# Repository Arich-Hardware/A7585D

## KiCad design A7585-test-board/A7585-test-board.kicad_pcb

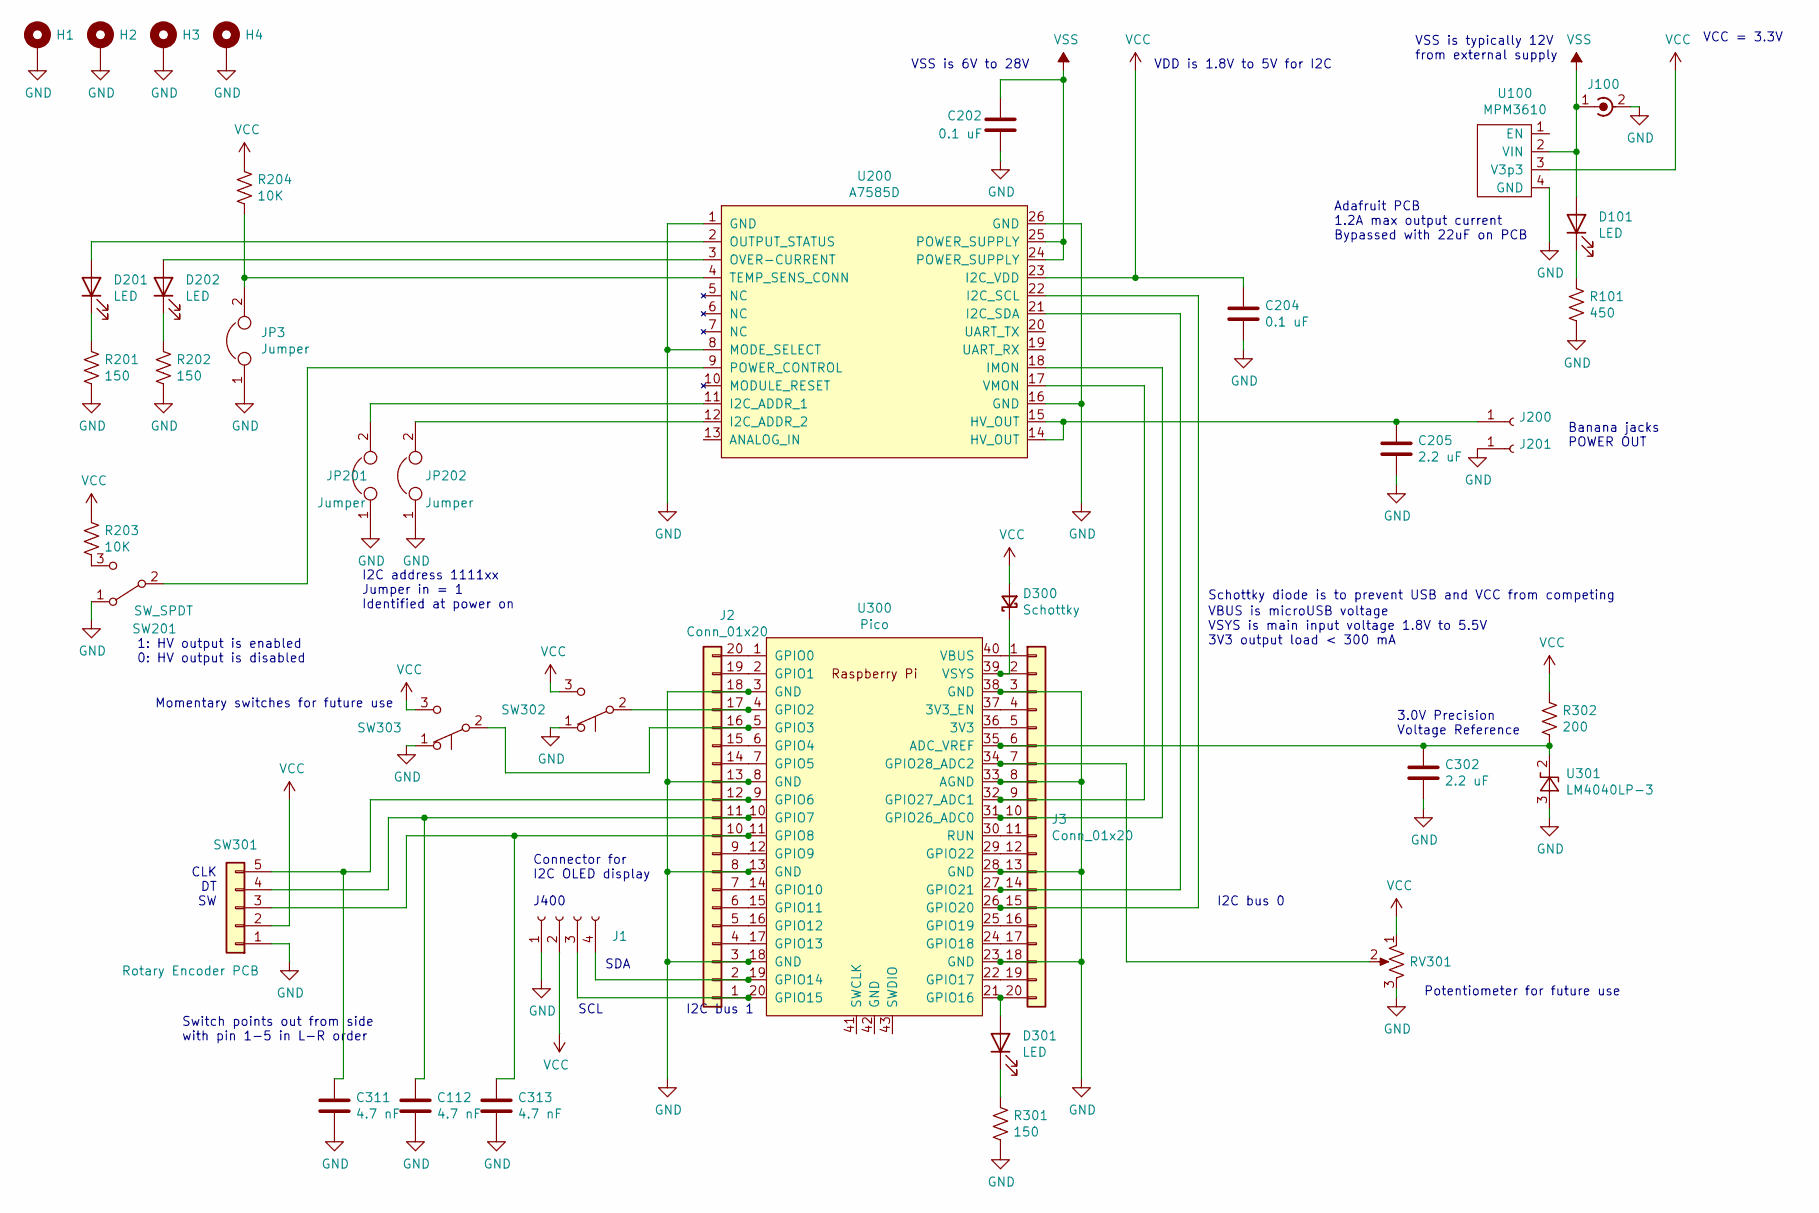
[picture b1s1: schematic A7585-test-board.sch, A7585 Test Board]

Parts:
C112, C311, C313: 4.7 nF; C_1206_3216Metric
C202, C204: 0.1 uF; C_1206_3216Metric
C205, C302: 2.2 uF; C_1206_3216Metric
D101, D201, D202, D301: LED; LED_D4.0mm
D300: Schottky; LED_D4.0mm
H1, H2, H3, H4: MountingHole_Pad; MountingHole_3.2mm_M3_Pad
J1: Conn_01x04_Female; Connector_Strip
J2, J3: Conn_01x20; PinHeader_1x20_P2.54mm_Vertical
J100: Conn_Coaxial_Power; BarrelJack_Horizontal
J200, J201: Conn_01x01_Female; Bannana_Jack_2pin
JP3, JP201, JP202: Jumper; PinHeader_1x02_P2.54mm_Vertical
R101: 450; R_1206_3216Metric
R201, R202, R301: 150; R_1206_3216Metric
R203, R204: 10K; R_1206_3216Metric
R302: 200; R_1206_3216Metric
RV301: R_POT_US; Potentiometer_Piher_T-16H_Single_Horizontal
SW201: SW_SPDT; SW_DIP_SPSTx01_Slide_9.78x4.72mm_W7.62mm_P2.54mm
SW301: Rotary Encoder PCB; PinHeader_1x05_P2.54mm_Vertical
SW302, SW303: SW_Push_SPDT; Push_Button
U100: MPM3610
U200: A7585D; A7585D_Board
U300: Pico; RPi_Pico_SMD_TH
U301: LM4040LP-3; TO-92_Inline

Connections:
GND: C112.2, C202.2, C204.2, C205.2, C302.2, C311.2, C313.2, H1.1, H2.1, H3.1, H4.1, J1.1, J2.3, J2.8, J2.13, J2.18, J3.3, J3.8, J3.13, J3.18, J100.2 (Ext), J201.1, JP3.1, JP201.1, JP202.1, R101.2, R201.2, R202.2, R301.2, RV301.3, SW201.1 (A), SW301.1, SW302.1 (A), SW303.1 (A), U100.4 (GND), U200.1 (GND), U200.8 (MODE_SELECT), U200.16 (GND), U200.26 (GND), U300.3 (GND), U300.8 (GND), U300.13 (GND), U300.18 (GND), U300.23 (GND), U300.28 (GND), U300.33 (AGND), U300.38 (GND), U301.3 (A)
unnamed: C112.1, J2.11, SW301.4, U300.10 (GPIO7)
unnamed: C205.1, J200.1, U200.14 (HV_OUT), U200.15 (HV_OUT)
unnamed: C302.1, J3.6, R302.2, U300.35 (ADC_VREF), U301.2 (K)
unnamed: C311.1, J2.12, SW301.5, U300.9 (GPIO6)
unnamed: C313.1, J2.10, SW301.3, U300.11 (GPIO8)
unnamed: D101.1 (K), R101.1
unnamed: D201.1 (K), R201.1
unnamed: D201.2 (A), U200.2 (OUTPUT_STATUS)
unnamed: D202.1 (K), R202.1
unnamed: D202.2 (A), U200.3 (OVER-CURRENT)
unnamed: D300.1 (K), J3.2, U300.39 (VSYS)
unnamed: D301.1 (K), R301.1
unnamed: D301.2 (A), J3.20, U300.21 (GPIO16)
unnamed: J1.3, J2.1, U300.20 (GPIO15)
unnamed: J1.4, J2.2, U300.19 (GPIO14)
unnamed: J2.4, U300.17 (GPIO13)
unnamed: J2.5, U300.16 (GPIO12)
unnamed: J2.6, U300.15 (GPIO11)
unnamed: J2.7, U300.14 (GPIO10)
unnamed: J2.9, U300.12 (GPIO9)
unnamed: J2.14, U300.7 (GPIO5)
unnamed: J2.15, U300.6 (GPIO4)
unnamed: J2.16, SW303.2 (B), U300.5 (GPIO3)
unnamed: J2.17, SW302.2 (B), U300.4 (GPIO2)
unnamed: J2.19, U300.2 (GPIO1)
unnamed: J2.20, U300.1 (GPIO0)
unnamed: J3.1, U300.40 (VBUS)
unnamed: J3.4, U300.37 (3V3_EN)
unnamed: J3.5, U300.36 (3V3)
unnamed: J3.7, RV301.2, U300.34 (GPIO28_ADC2)
unnamed: J3.9, U200.17 (VMON), U300.32 (GPIO27_ADC1)
unnamed: J3.10, U200.18 (IMON), U300.31 (GPIO26_ADC0)
unnamed: J3.11, U300.30 (RUN)
unnamed: J3.12, U300.29 (GPIO22)
unnamed: J3.14, U200.21 (I2C_SDA), U300.27 (GPIO21)
unnamed: J3.15, U200.22 (I2C_SCL), U300.26 (GPIO20)
unnamed: J3.16, U300.25 (GPIO19)
unnamed: J3.17, U300.24 (GPIO18)
unnamed: J3.19, U300.22 (GPIO17)
unnamed: JP3.2, R204.2, U200.4 (TEMP_SENS_CONN)
unnamed: JP201.2, U200.11 (I2C_ADDR_1)
unnamed: JP202.2, U200.12 (I2C_ADDR_2)
unnamed: R203.2, SW201.3 (C)
unnamed: SW201.2 (B), U200.9 (POWER_CONTROL)
VCC: C204.1, D300.2 (A), J1.2, R203.1, R204.1, R302.1, RV301.1, SW301.2, SW302.3 (C), SW303.3 (C), U100.3 (V3p3), U200.23 (I2C_VDD)
VSS: C202.1, D101.2 (A), J100.1 (In), U100.2 (VIN), U200.24 (POWER_SUPPLY), U200.25 (POWER_SUPPLY)

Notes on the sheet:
VDD is 1.8V to 5V for I2C
VSS is 6V to 28V
VBUS is microUSB voltage VSYS is main input voltage 1.8V to 5.5V 3V3 output load < 300 mA
Adafruit PCB 1.2A max output current Bypassed with 22uF on PCB
VCC = 3.3V
I2C address 1111xx Jumper in = 1 Identified at power on
1: HV output is enabled 0: HV output is disabled
VSS is typically 12V from external supply
Schottky diode is to prevent USB and VCC from competing
Momentary switches for future use
Potentiometer for future use
I2C bus 0
SCL
SDA
J400
Connector for I2C OLED display
I2C bus 1
Switch points out from side with pin 1-5 in L-R order
CLK DT SW
Banana jacks POWER OUT
3.0V Precision Voltage Reference

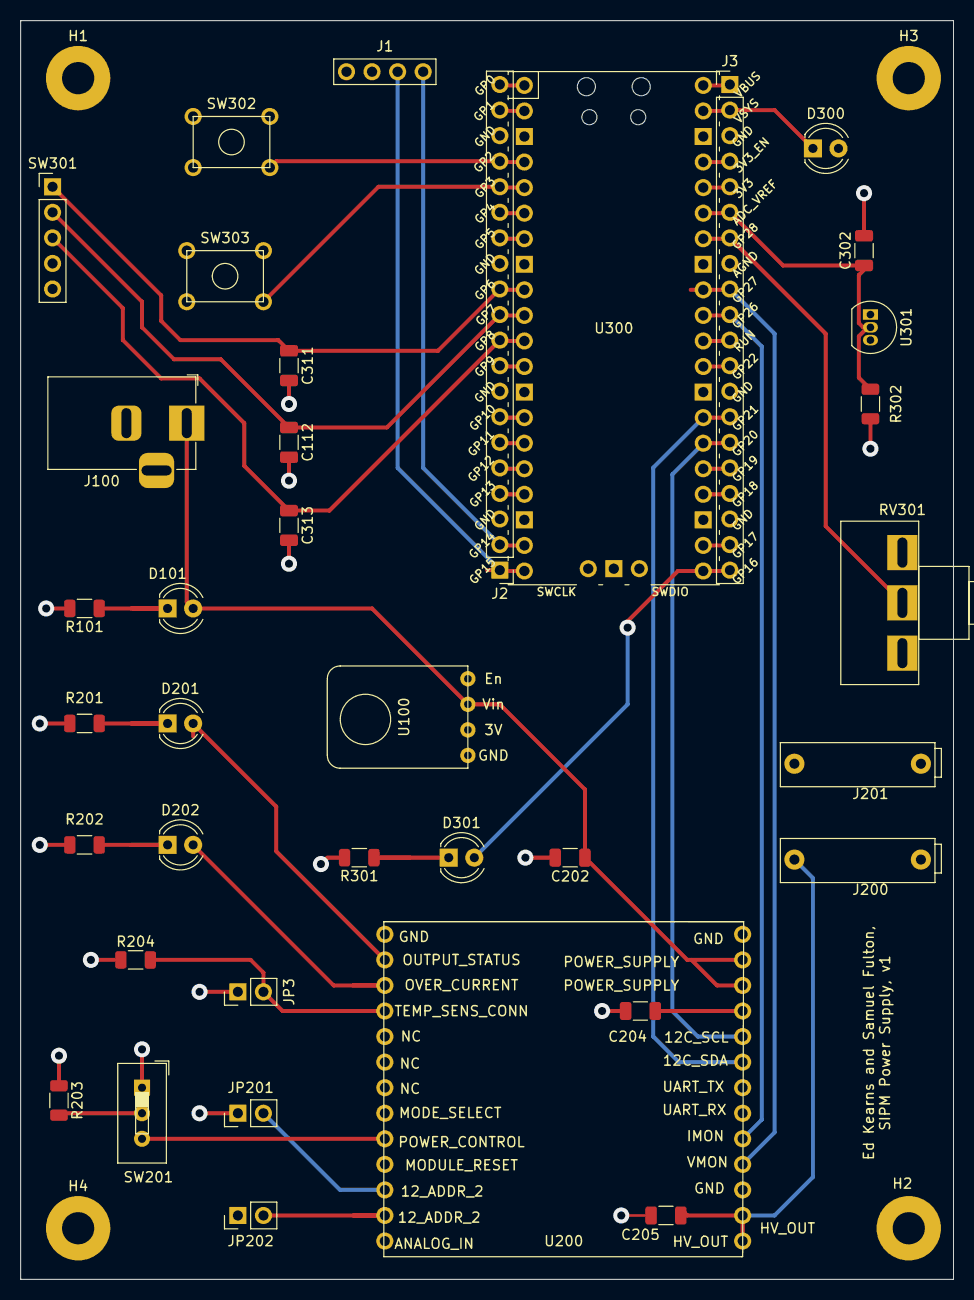
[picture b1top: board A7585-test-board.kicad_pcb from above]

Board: 4 copper layers, 92.7 x 125.1 mm, 41 parts (0 on the bottom side), 47 nets.

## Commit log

2021-08-02 Minor schematic changes. Layout V1
2021-08-03 Fixed power planes
2021-08-03 Grounded mounting holes. Fixed power plane
2021-08-09 New Banana Jacks
2021-09-13 New circuit diagram with rotary encoder and precision voltage reference.
2021-10-05 Reorganized Library
2021-10-11 Reorganizing
2021-10-11 Library-organized
2021-10-11 Library-Reoganized
2021-10-26 Final Updates
2021-10-29 Create new
